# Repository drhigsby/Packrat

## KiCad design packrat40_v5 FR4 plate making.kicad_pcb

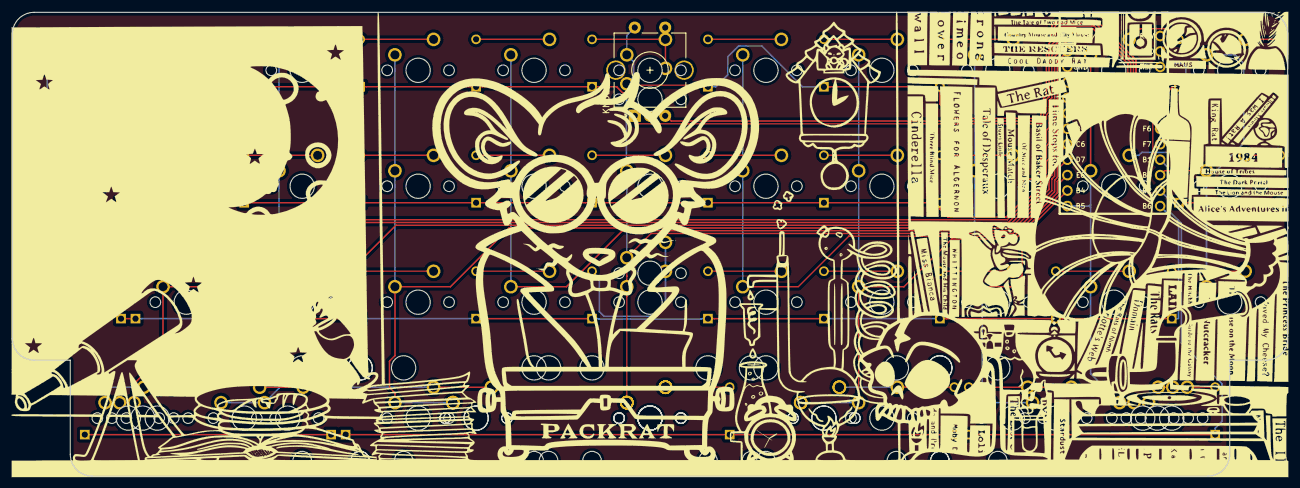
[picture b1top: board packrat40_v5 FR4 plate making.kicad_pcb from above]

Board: 2 copper layers, 209.6 x 76.2 mm, 98 parts (1 on the bottom side), 59 nets.

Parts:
D1, D2, D3, D4, D5, D6, D7, D8, D9, D10, D11, D12, D13, D14, D15, D16, D17, D18, D19, D20, D21, D22, D23, D24, D25, D26, D27, D28, D29, D30, D31, D32, D33, D34, D35, D36, D37, D38, D39, D40: D_Small; Diode-Hybrid-Back
KNOB1: Rotary_Encoder_Switch; RotaryEncoder_Alps_EC11E-Switch_Vertical_H20mm_CircularMoun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
MX1, MX2, MX3, MX4, MX5, MX6, MX7, MX8, MX9, MX10, MX11, MX12, MX13, MX14, MX15, MX16, MX17, MX18, MX19, MX20, MX21, MX22, MX23, MX24, MX25, MX26, MX27, MX28, MX29, MX30, MX31, MX32, MX33, MX34-1u1, MX35-1u1, MX36-1u1, MX37, MX38-1u1, MX39-1u1, MX40-1u1: MX-NoLED; MXOnly-1U-NoLED
MX6-1.5u1, MX28-1.5u1: MX-NoLED; MXOnly-1.5U-Vertical-NoLED
MX34, MX35, MX39, MX40: MX-NoLED; MXOnly-1.25U-NoLED
MX34-1.5u1, MX40-1.5u1: MX-NoLED; MXOnly-1.5U-NoLED
MX36, MX38: MX-NoLED; MXOnly-2U-ReversedStabilizers-NoLED
MX36-3u1, MX37-3u1, MX38-3u1: MX-NoLED; MXOnly-3U-ReversedStabilizers-NoLED
MX37-6u1: MX-NoLED; MXOnly-6U-Centered-ReversedStabilizers-NoLED
MX37-7u1: MX-NoLED; MXOnly-7U-ReversedStabilizers-NoLED
SW1: SW_Push; SKQG-1155865
U1: ProMicro; ArduinoProMicro

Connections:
COL0: MX1.1, MX12.1, MX23.1, U1.1
COL1: MX2.1, MX13.1, MX24.1, MX34.1, MX34-1.5u1.1, MX34-1u1.1, U1.2
COL2: MX3.1, MX14.1, MX25.1, MX35.1, MX35-1u1.1, U1.5
COL3: MX4.1, MX15.1, MX26.1, MX36.1, MX36-1u1.1, MX36-3u1.1, U1.6
COL4: MX5.1, MX16.1, MX27.1, U1.7
COL5: KNOB1.S2, MX6.1, MX6-1.5u1.1, MX17.1, MX28.1, MX28-1.5u1.1, MX37.1, MX37-3u1.1, MX37-6u1.1, MX37-7u1.1, U1.8
COL6: MX7.1, MX18.1, MX29.1, U1.9
COL7: MX8.1, MX19.1, MX30.1, MX38.1, MX38-1u1.1, MX38-3u1.1, U1.10
COL8: MX9.1, MX20.1, MX31.1, MX39.1, MX39-1u1.1, U1.11
COL9: MX10.1, MX21.1, MX32.1, MX40.1, MX40-1.5u1.1, MX40-1u1.1, U1.12
COL10: MX11.1, MX22.1, MX33.1, U1.15
GND: KNOB1.C, SW1.1, U1.3, U1.4, U1.23
M1: D6.2, KNOB1.S1, MX6.2, MX6-1.5u1.2
unnamed: D1.2, MX1.2
unnamed: D2.2, MX2.2
unnamed: D3.2, MX3.2
unnamed: D4.2, MX4.2
unnamed: D5.2, MX5.2
unnamed: D7.2, MX7.2
unnamed: D8.2, MX8.2
unnamed: D9.2, MX9.2
unnamed: D10.2, MX10.2
unnamed: D11.2, MX11.2
unnamed: D12.2, MX12.2
unnamed: D13.2, MX13.2
unnamed: D14.2, MX14.2
unnamed: D15.2, MX15.2
unnamed: D16.2, MX16.2
unnamed: D17.2, MX17.2
unnamed: D18.2, MX18.2
unnamed: D19.2, MX19.2
unnamed: D20.2, MX20.2
unnamed: D21.2, MX21.2
unnamed: D22.2, MX22.2
unnamed: D23.2, MX23.2
unnamed: D24.2, MX24.2
unnamed: D25.2, MX25.2
unnamed: D26.2, MX26.2
unnamed: D27.2, MX27.2
unnamed: D28.2, MX28.2, MX28-1.5u1.2
unnamed: D29.2, MX29.2
unnamed: D30.2, MX30.2
unnamed: D31.2, MX31.2
unnamed: D32.2, MX32.2
unnamed: D33.2, MX33.2
unnamed: D34.2, MX34.2, MX34-1.5u1.2, MX34-1u1.2
unnamed: D35.2, MX35.2, MX35-1u1.2
unnamed: D36.2, MX36.2, MX36-1u1.2, MX36-3u1.2
unnamed: D37.2, MX37.2, MX37-3u1.2, MX37-6u1.2, MX37-7u1.2
unnamed: D38.2, MX38.2, MX38-1u1.2, MX38-3u1.2
unnamed: D39.2, MX39.2, MX39-1u1.2
unnamed: D40.2, MX40.2, MX40-1.5u1.2, MX40-1u1.2
PM1: KNOB1.B, U1.20
PM2: KNOB1.A, U1.19
ROW0: D1.1, D2.1, D3.1, D4.1, D5.1, D6.1, D7.1, D8.1, D9.1, D10.1, D11.1, U1.17
ROW1: D12.1, D13.1, D14.1, D15.1, D16.1, D17.1, D18.1, D19.1, D20.1, D21.1, D22.1, U1.16
ROW2: D23.1, D24.1, D25.1, D26.1, D27.1, D28.1, D29.1, D30.1, D31.1, D32.1, D33.1, U1.13
ROW3: D34.1, D35.1, D36.1, D37.1, D38.1, D39.1, D40.1, U1.14
RST: SW1.2, U1.22

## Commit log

2021-03-25 first push
2021-03-25 added hardware list
